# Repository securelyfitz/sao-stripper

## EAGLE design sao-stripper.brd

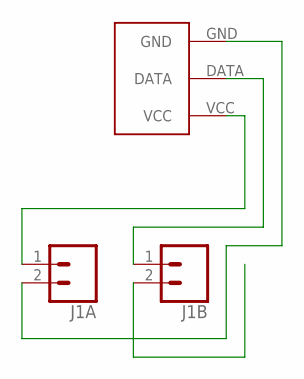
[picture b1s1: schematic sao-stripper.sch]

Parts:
J1A, J1B: CONN_02LOCK; 1X02_LOCK
U$1: LEDSTRIP

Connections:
GND: J1A.2, U$1.GND
SCL: J1B.2
SDA: J1B.1, U$1.DATA
VCC: J1A.1, U$1.VCC

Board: 2 copper layers, 3 parts (0 on the bottom side), 3 nets, no tracks yet.

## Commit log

2018-08-09 boards, schematics, cam, gerbers, and zips...

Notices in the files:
parts and their libraries:
SparkFun-Connectors: Licensing: Creative Commons ShareAlike 4.0 International - https://creativecommons.org/licenses/by-sa/4.0
